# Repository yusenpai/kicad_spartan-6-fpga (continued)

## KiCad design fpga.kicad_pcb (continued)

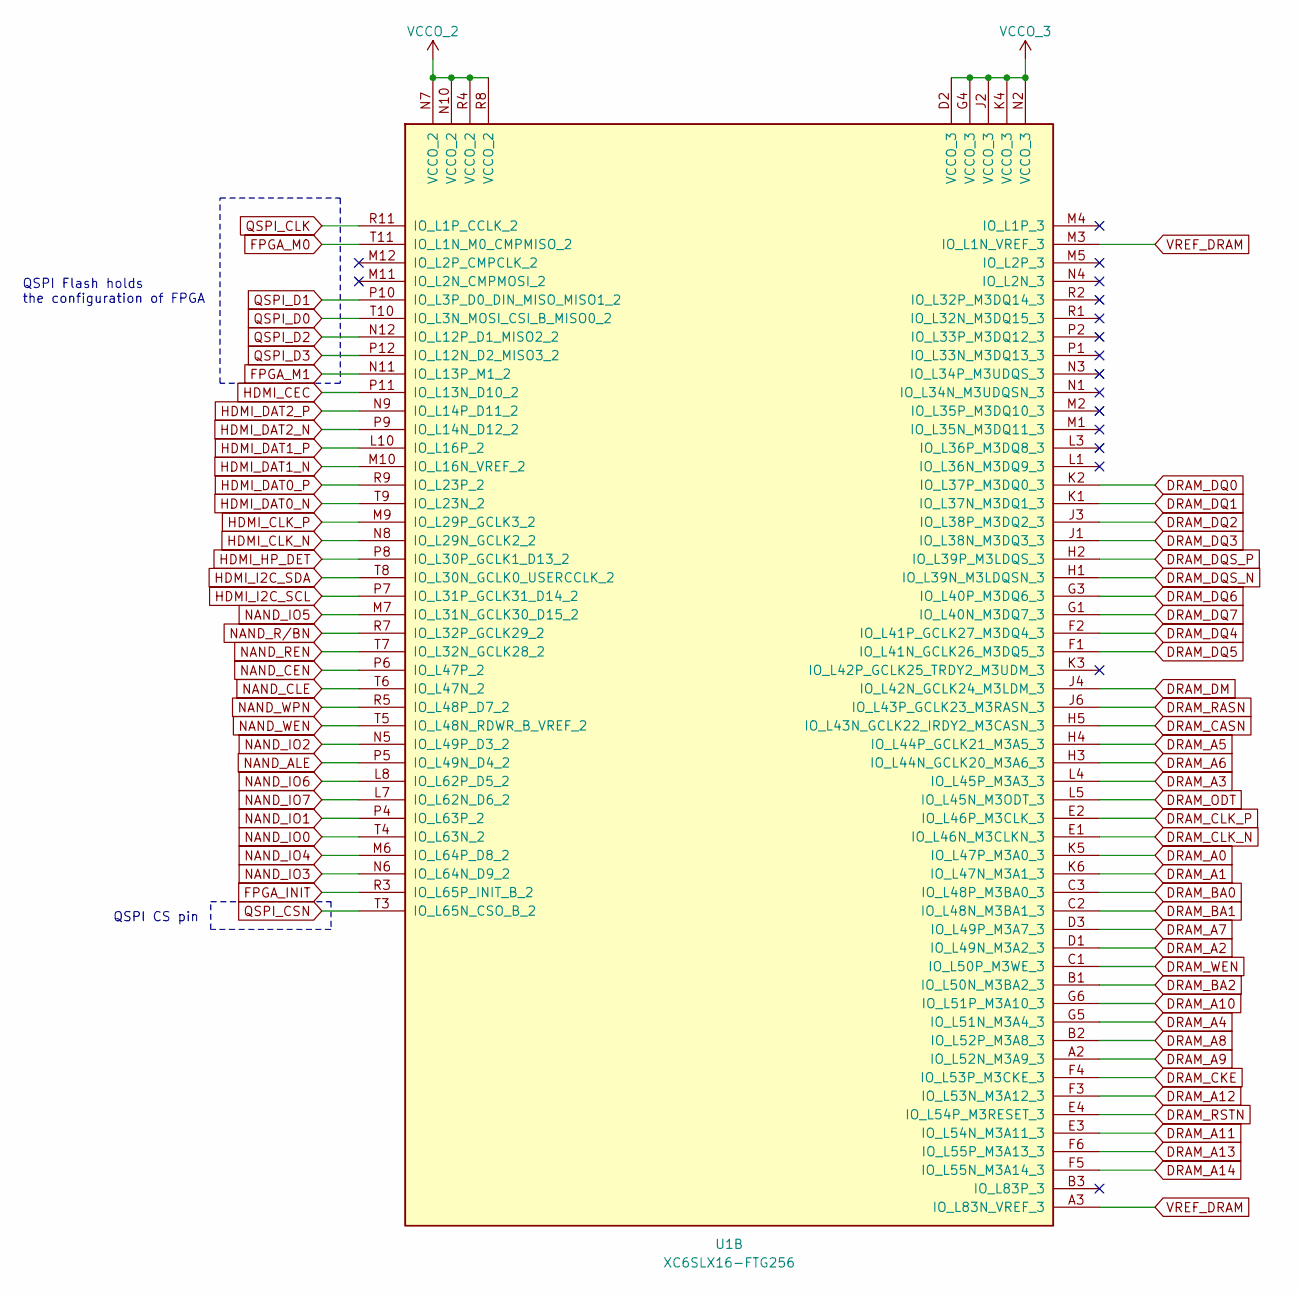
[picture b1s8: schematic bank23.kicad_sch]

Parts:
U1: XC6SLX16-FTG256; BGA-256_17.0x17.0mm_Layout16x16_P1.0mm_Ball0.5mm_Pad0.4mm_N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

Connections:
+1V35: U1.D2 (VCCO_3), U1.G4 (VCCO_3), U1.J2 (VCCO_3), U1.K4 (VCCO_3), U1.N2 (VCCO_3); also elsewhere on the board
+3V3: U1.N7 (VCCO_2), U1.N10 (VCCO_2), U1.R4 (VCCO_2), U1.R8 (VCCO_2); also elsewhere on the board
DRAM_A0: U1.K5 (IO_L47P_M3A0_3); also elsewhere on the board
DRAM_A1: U1.K6 (IO_L47N_M3A1_3); also elsewhere on the board
DRAM_A2: U1.D1 (IO_L49N_M3A2_3); also elsewhere on the board
DRAM_A3: U1.L4 (IO_L45P_M3A3_3); also elsewhere on the board
DRAM_A4: U1.G5 (IO_L51N_M3A4_3); also elsewhere on the board
DRAM_A5: U1.H4 (IO_L44P_GCLK21_M3A5_3); also elsewhere on the board
DRAM_A6: U1.H3 (IO_L44N_GCLK20_M3A6_3); also elsewhere on the board
DRAM_A7: U1.D3 (IO_L49P_M3A7_3); also elsewhere on the board
DRAM_A8: U1.B2 (IO_L52P_M3A8_3); also elsewhere on the board
DRAM_A9: U1.A2 (IO_L52N_M3A9_3); also elsewhere on the board
DRAM_A10: U1.G6 (IO_L51P_M3A10_3); also elsewhere on the board
DRAM_A11: U1.E3 (IO_L54N_M3A11_3); also elsewhere on the board
DRAM_A12: U1.F3 (IO_L53N_M3A12_3); also elsewhere on the board
DRAM_A13: U1.F6 (IO_L55P_M3A13_3); also elsewhere on the board
DRAM_A14: U1.F5 (IO_L55N_M3A14_3); also elsewhere on the board
DRAM_BA0: U1.C3 (IO_L48P_M3BA0_3); also elsewhere on the board
DRAM_BA1: U1.C2 (IO_L48N_M3BA1_3); also elsewhere on the board
DRAM_BA2: U1.B1 (IO_L50N_M3BA2_3); also elsewhere on the board
DRAM_CASN: U1.H5 (IO_L43N_GCLK22_IRDY2_M3CASN_3); also elsewhere on the board
DRAM_CKE: U1.F4 (IO_L53P_M3CKE_3); also elsewhere on the board
DRAM_CLK_N: U1.E1 (IO_L46N_M3CLKN_3); also elsewhere on the board
DRAM_CLK_P: U1.E2 (IO_L46P_M3CLK_3); also elsewhere on the board
DRAM_DM: U1.J4 (IO_L42N_GCLK24_M3LDM_3); also elsewhere on the board
DRAM_DQ0: U1.K2 (IO_L37P_M3DQ0_3); also elsewhere on the board
DRAM_DQ1: U1.K1 (IO_L37N_M3DQ1_3); also elsewhere on the board
DRAM_DQ2: U1.J3 (IO_L38P_M3DQ2_3); also elsewhere on the board
DRAM_DQ3: U1.J1 (IO_L38N_M3DQ3_3); also elsewhere on the board
DRAM_DQ4: U1.F2 (IO_L41P_GCLK27_M3DQ4_3); also elsewhere on the board
DRAM_DQ5: U1.F1 (IO_L41N_GCLK26_M3DQ5_3); also elsewhere on the board
DRAM_DQ6: U1.G3 (IO_L40P_M3DQ6_3); also elsewhere on the board
DRAM_DQ7: U1.G1 (IO_L40N_M3DQ7_3); also elsewhere on the board
DRAM_DQS_N: U1.H1 (IO_L39N_M3LDQSN_3); also elsewhere on the board
DRAM_DQS_P: U1.H2 (IO_L39P_M3LDQS_3); also elsewhere on the board
DRAM_ODT: U1.L5 (IO_L45N_M3ODT_3); also elsewhere on the board
DRAM_RASN: U1.J6 (IO_L43P_GCLK23_M3RASN_3); also elsewhere on the board
DRAM_RSTN: U1.E4 (IO_L54P_M3RESET_3); also elsewhere on the board
DRAM_WEN: U1.C1 (IO_L50P_M3WE_3); also elsewhere on the board
FPGA_INIT: U1.R3 (IO_L65P_INIT_B_2); also elsewhere on the board
FPGA_M0: U1.T11 (IO_L1N_M0_CMPMISO_2); also elsewhere on the board
FPGA_M1: U1.N11 (IO_L13P_M1_2); also elsewhere on the board
HDMI_CEC: U1.P11 (IO_L13N_D10_2); also elsewhere on the board
HDMI_CLK_N: U1.N8 (IO_L29N_GCLK2_2); also elsewhere on the board
HDMI_CLK_P: U1.M9 (IO_L29P_GCLK3_2); also elsewhere on the board
HDMI_DAT0_N: U1.T9 (IO_L23N_2); also elsewhere on the board
HDMI_DAT0_P: U1.R9 (IO_L23P_2); also elsewhere on the board
HDMI_DAT1_N: U1.M10 (IO_L16N_VREF_2); also elsewhere on the board
HDMI_DAT1_P: U1.L10 (IO_L16P_2); also elsewhere on the board
HDMI_DAT2_N: U1.P9 (IO_L14N_D12_2); also elsewhere on the board
HDMI_DAT2_P: U1.N9 (IO_L14P_D11_2); also elsewhere on the board
HDMI_HP_DET: U1.P8 (IO_L30P_GCLK1_D13_2); also elsewhere on the board
HDMI_I2C_SCL: U1.P7 (IO_L31P_GCLK31_D14_2); also elsewhere on the board
HDMI_I2C_SDA: U1.T8 (IO_L30N_GCLK0_USERCCLK_2); also elsewhere on the board
NAND_ALE: U1.P5 (IO_L49N_D4_2); also elsewhere on the board
NAND_CEN: U1.P6 (IO_L47P_2); also elsewhere on the board
NAND_CLE: U1.T6 (IO_L47N_2); also elsewhere on the board
NAND_IO0: U1.T4 (IO_L63N_2); also elsewhere on the board
NAND_IO1: U1.P4 (IO_L63P_2); also elsewhere on the board
NAND_IO2: U1.N5 (IO_L49P_D3_2); also elsewhere on the board
NAND_IO3: U1.N6 (IO_L64N_D9_2); also elsewhere on the board
NAND_IO4: U1.M6 (IO_L64P_D8_2); also elsewhere on the board
NAND_IO5: U1.M7 (IO_L31N_GCLK30_D15_2); also elsewhere on the board
NAND_IO6: U1.L8 (IO_L62P_D5_2); also elsewhere on the board
NAND_IO7: U1.L7 (IO_L62N_D6_2); also elsewhere on the board
NAND_REN: U1.T7 (IO_L32N_GCLK28_2); also elsewhere on the board
NAND_R/BN: U1.R7 (IO_L32P_GCLK29_2); also elsewhere on the board
NAND_WEN: U1.T5 (IO_L48N_RDWR_B_VREF_2); also elsewhere on the board
NAND_WPN: U1.R5 (IO_L48P_D7_2); also elsewhere on the board
QSPI_CLK: U1.R11 (IO_L1P_CCLK_2); also elsewhere on the board
QSPI_CSN: U1.T3 (IO_L65N_CSO_B_2); also elsewhere on the board
QSPI_D0: U1.T10 (IO_L3N_MOSI_CSI_B_MISO0_2); also elsewhere on the board
QSPI_D1: U1.P10 (IO_L3P_D0_DIN_MISO_MISO1_2); also elsewhere on the board
QSPI_D2: U1.N12 (IO_L12P_D1_MISO2_2); also elsewhere on the board
QSPI_D3: U1.P12 (IO_L12N_D2_MISO3_2); also elsewhere on the board
VREF_DRAM: U1.A3 (IO_L83N_VREF_3), U1.M3 (IO_L1N_VREF_3); also elsewhere on the board

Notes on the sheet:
QSPI Flash holds the configuration of FPGA
QSPI CS pin

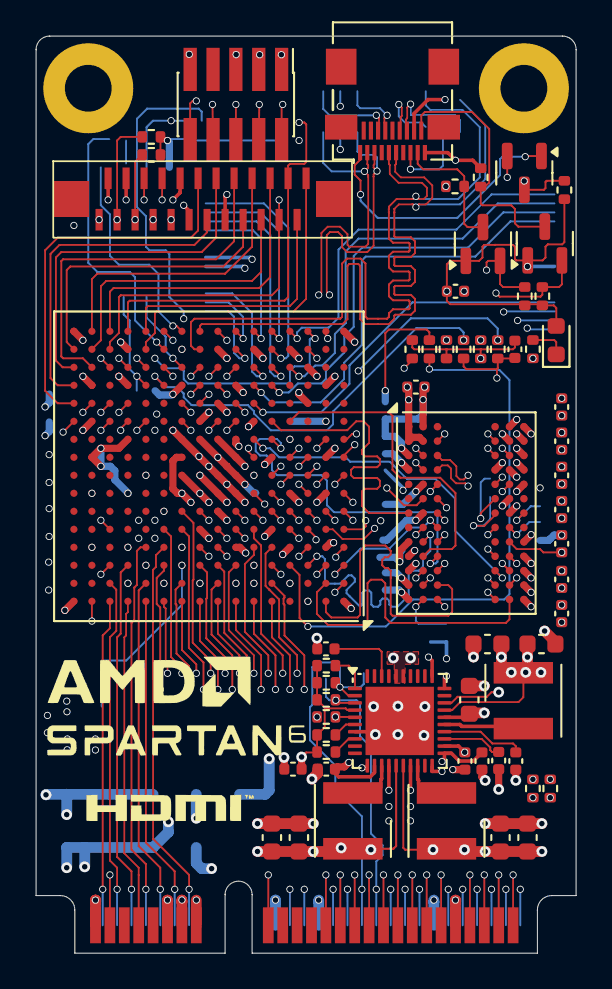
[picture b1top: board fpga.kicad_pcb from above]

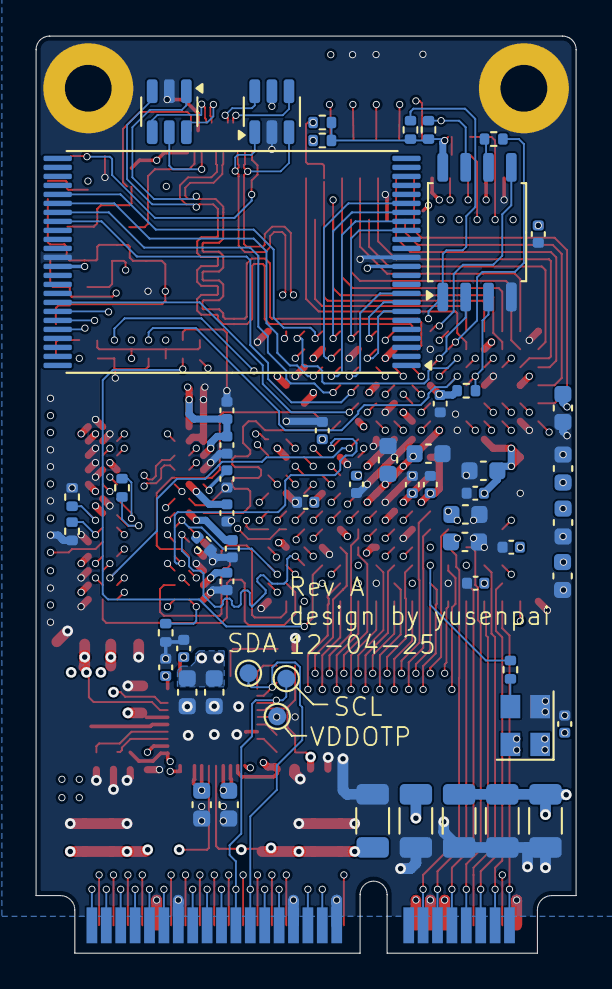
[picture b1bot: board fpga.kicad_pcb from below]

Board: 8 copper layers, 30.0 x 51.0 mm, 117 parts (57 on the bottom side), 167 nets.
